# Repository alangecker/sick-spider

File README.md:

# SICK Spider
A new board design for the amazing [COATI Spider project](https://coati.pimienta.org/electronics/spider/), a small portable device for simultaneous interpretation.

## Changes compared to the COATI spider
- way less noise
- battery level indicator
- better gain control range
- USB-C port for power supply
- way longer battery runtime (8-50h)
- easier available components

## Costs
- roughly 20€ for a spider without accessories
- An existing COATI spider case can be reused, only one additional cutout for the USB-C port is required.

## Case
The files for 3D printing a case can be found here:
https://github.com/alangecker/spider-case

## Documents & How-To's

#### Version 1.2 (Documents work in progress)
- [Changelog](./CHANGELOG.md)
- Ordering
  * [Parts list](https://pad.kanthaus.online/sick-spider-parts-list?view)
  * Gerber files: [JLCPCB](https://alangecker.github.io/sick-spider/output/1.2/JLCPCB/spider2-JLCPCB.zip)
- Building instructions
    * [Part 1: soldering “SMD” components](https://pad.kanthaus.online/sick-spider-instructions-part1?view)
    * [Part 2: soldering "trough hole" components](https://pad.kanthaus.online/sick-spider-instructions-part2?view)
- [Debugging](https://pad.kanthaus.online/sick-spider-instructions-debugging?view)
- [Boardview and BOM](https://alangecker.github.io/sick-spider/output/1.2/spider2-ibom.html)
- [Schematic](https://alangecker.github.io/sick-spider/output/1.2/spider2-schematic.pdf)

#### Version 1.1
- [Changelog](./CHANGELOG.md)
- Ordering
  * [Parts list](./docs/v1.1/partslist.md)
  * Gerber files: [JLCPCB](https://alangecker.github.io/sick-spider/output/1.1c/JLCPCB/spider2-JLCPCB.zip)
- Building instructions
    * [Part 1: soldering “SMD” components](./docs/v1.1/part1-smd.md)
    * [Part 2: soldering "trough hole" components](./docs/v1.1/part2-throughhole.md)
- [Boardview and BOM](https://alangecker.github.io/sick-spider/output/1.1c/spider2-ibom.html)
- [Schematic](https://alangecker.github.io/sick-spider/output/1.1c/spider2-schematic.pdf)

#### Version 1.0
- Ordering
  * [Parts list](./docs/v1.0/partslist.md)
  * Gerber files: [JLCPCB](https://alangecker.github.io/sick-spider/output/1.0/JLCPCB/spider2-JLCPCB.zip)
- Building instructions
    * [Part 1: soldering “SMD” components](./docs/v1.0/part1-smd.md)
    * [Part 2: soldering "trough hole" components](./docs/v1.0/part2-throughhole.md)
    * [Part 3: building the case](https://pad.kanthaus.online/sick-spider-instructions-part3?view)
- [Debugging](./docs/v1.0/debugging.md)
- [Boardview and BOM](https://alangecker.github.io/sick-spider/output/1.0/spider2-ibom.html)
- [Schematic](https://alangecker.github.io/sick-spider/output/1.0/spider2-schematic.pdf)

## License
GPLv3 (=open source♥)

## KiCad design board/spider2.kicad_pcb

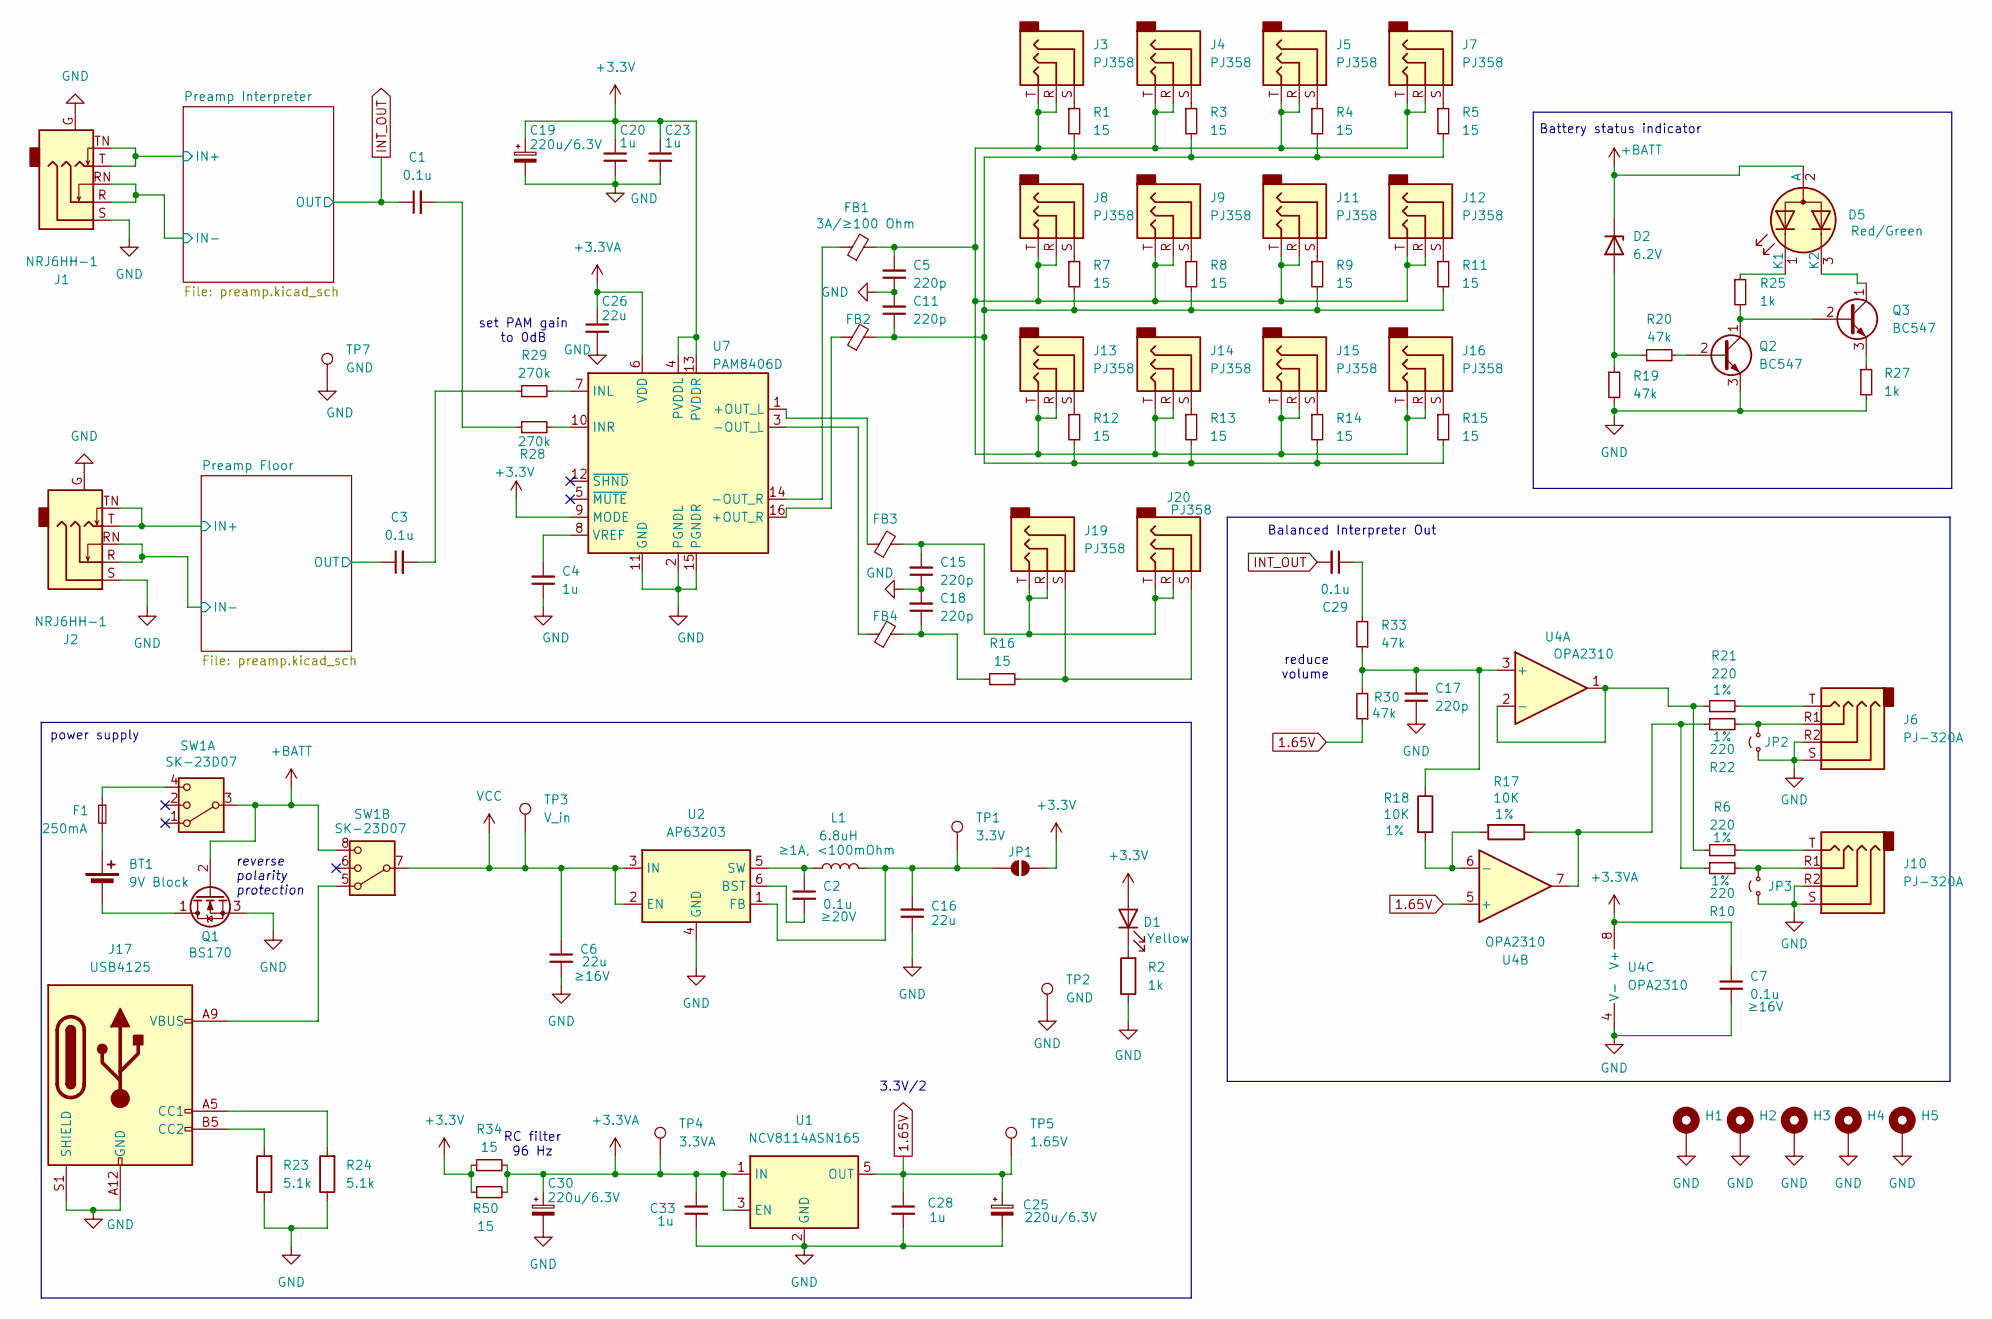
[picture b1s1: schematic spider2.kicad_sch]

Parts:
BT1: 9V Block; PinHeader_1x02_P2.54mm_Vertical
C1, C3, C7, C29: 0.1u; C_Disc_D3.0mm_W2.0mm_P2.50mm
C2: 0.1u; C_1206_3216Metric_Pad1.33x1.80mm_HandSolder
C4, C20, C23, C28, C33: 1u; C_Disc_D3.0mm_W2.0mm_P2.50mm
C5, C11, C15, C17, C18: 220p; C_Disc_D3.0mm_W2.0mm_P2.50mm
C6, C16, C26: 22u; C_1206_3216Metric_Pad1.33x1.80mm_HandSolder
C19, C25, C30: 220u/6.3V; CP_Radial_D6.3mm_P2.50mm
D1: Yellow; LED_D5.0mm_FlatTop
D2: 6.2V; D_DO-35_SOD27_P7.62mm_Horizontal
D5: Red/Green; LED_D5.0mm-3
F1: 250mA; Fuse_1206_3216Metric_Pad1.42x1.75mm_HandSolder
FB1, FB2, FB3, FB4: 3A/≥100 Ohm; L_Axial_L7.0mm_D3.3mm_P10.16mm_Horizontal_Fastron_MICC
H1, H2, H3, H4, H5: MountingHole_3.2mm_M3_Pad_Via
J1, J2: NRJ6HH-1; Jack_6.35mm_Neutrik_NRJ6HH-1_Horizontal
J3, J4, J5, J7, J8, J9, J11, J12, J13, J14, J15, J16, J19, J20: PJ358; Jack_3.5mm_Hybrid_PJ358_20-1655
J6, J10: PJ-320A; Jack_3.5mm_PJ320A
J17: USB4125; USB_C_Receptacle_GCT_USB4125-xx-x_6P_TopMnt_Horizontal
JP1, JP2, JP3: SolderJumper-2_P1.3mm_Open_RoundedPad1.0x1.5mm
L1: 6.8uH; L_Bourns_SRN6045TA
Q1: BS170; TO-92_Inline_Wide
Q2, Q3: BC547; TO-92_Inline_Wide
R1, R3, R4, R5, R7, R8, R9, R11, R12, R13, R14, R15, R16, R34, R50: 15; R_Axial_DIN0207_L6.3mm_D2.5mm_P10.16mm_Horizontal
R2, R25, R27: 1k; R_Axial_DIN0207_L6.3mm_D2.5mm_P10.16mm_Horizontal
R6, R10, R21, R22: 220; R_Axial_DIN0204_L3.6mm_D1.6mm_P5.08mm_Horizontal
R17, R18: 10K; R_Axial_DIN0204_L3.6mm_D1.6mm_P5.08mm_Horizontal
R19, R20, R30, R33: 47k; R_Axial_DIN0207_L6.3mm_D2.5mm_P10.16mm_Horizontal
R23, R24: 5.1k; R_Axial_DIN0207_L6.3mm_D2.5mm_P10.16mm_Horizontal
R28, R29: 270k; R_Axial_DIN0207_L6.3mm_D2.5mm_P7.62mm_Horizontal
SW1: SK-23D07
TP1: 3.3V; TestPoint_THTPad_1.5x1.5mm_Drill0.7mm
TP2: GND; TestPoint_THTPad_2.5x2.5mm_Drill1.2mm
TP3: V_in; TestPoint_THTPad_1.5x1.5mm_Drill0.7mm
TP4: 3.3VA; TestPoint_THTPad_1.5x1.5mm_Drill0.7mm
TP5: 1.65V; TestPoint_THTPad_1.5x1.5mm_Drill0.7mm
TP7: GND; TestPoint_THTPad_4.0x4.0mm_Drill2.0mm
U1: NCV8114ASN165; TSOT-23-5
U2: AP63203; TSOT-23-6
U4: OPA2310; SOIC-8_3.9x4.9mm_P1.27mm
U7: PAM8406D; SOP-16_3.9x9.9mm_P1.27mm

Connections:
1.65V: C25.1, C28.1, R30.1, TP5.1, U1.5 (OUT), U4.5 (+); also elsewhere on the board
+3.3V: C19.1, C20.1, C23.1, D1.2 (A), JP1.2 (B), R34.1, R50.1, U7.4 (PVDDL), U7.9 (MODE), U7.13 (PVDDR)
+3.3VA: C7.1, C26.1, C30.1, C33.1, R34.2, R50.2, TP4.1, U1.1 (IN), U1.3 (EN), U4.8 (V+), U7.6 (VDD); also elsewhere on the board
+BATT: D2.1 (K), D5.2 (A), Q1.2 (G), SW1.3, SW1.8
/Preamp Floor/IN+: J2.T, J2.TN; also elsewhere on the board
/Preamp Floor/IN-: J2.R, J2.RN; also elsewhere on the board
/Preamp Floor/OUT: C3.1; also elsewhere on the board
/Preamp Interpreter/IN+: J1.T, J1.TN; also elsewhere on the board
/Preamp Interpreter/IN-: J1.R, J1.RN; also elsewhere on the board
GND: C4.1, C5.1, C6.2, C7.2, C11.2, C15.1, C16.1, C17.1, C18.2, C19.2, C20.2, C23.2, C25.2, C26.2, C28.2, C30.2, C33.2, H1.1, H2.1, H3.1, H4.1, H5.1, J1.G, J1.S, J2.G, J2.S, J6.R2, J6.S, J10.R2, J10.S, J17.A12 (GND), J17.B12 (GND), J17.S1 (SHIELD), JP2.1 (A), JP3.1 (A), Q1.3 (S), Q2.3 (E), R2.1, R19.2, R23.1, R24.1, R27.2, TP2.1, TP7.1, U1.2 (GND), U2.4 (GND), U4.4 (V-), U7.2 (PGNDL), U7.11 (GND), U7.15 (PGNDR); also elsewhere on the board
INT_OUT: C1.1, C29.2; also elsewhere on the board
unnamed: BT1.1 (+), F1.2
unnamed: BT1.2 (-), Q1.1 (D)
unnamed: C1.2, R28.1
unnamed: C3.2, R29.1
unnamed: C5.2, FB1.2, J3.R, J3.T, J4.R, J4.T, J5.R, J5.T, J7.R, J7.T, J8.R, J8.T, J9.R, J9.T, J11.R, J11.T, J12.R, J12.T, J13.R, J13.T, J14.R, J14.T, J15.R, J15.T, J16.R, J16.T
unnamed: C11.1, FB2.2, R1.2, R3.2, R4.2, R5.2, R7.2, R8.2, R9.2, R11.2, R12.2, R13.2, R14.2, R15.2
unnamed: C15.2, FB3.2, J19.R, J19.T, J20.R, J20.T
unnamed: C18.1, FB4.2, R16.1
unnamed: C29.1, R33.2
unnamed: D1.1 (K), R2.2
unnamed: D2.2 (A), R19.1, R20.1
unnamed: D5.1 (K1), R25.1
unnamed: D5.3 (K2), Q3.1 (C)
unnamed: F1.1, SW1.4
unnamed: J3.S, R1.1
unnamed: J4.S, R3.1
unnamed: J5.S, R4.1
unnamed: J6.T, R21.2
unnamed: J7.S, R5.1
unnamed: J8.S, R7.1
unnamed: J9.S, R8.1
unnamed: J10.T, R6.2
unnamed: J11.S, R9.1
unnamed: J12.S, R11.1
unnamed: J13.S, R12.1
unnamed: J14.S, R13.1
unnamed: J15.S, R14.1
unnamed: J16.S, R15.1
unnamed: J17.A5 (CC1), R24.2
unnamed: J17.B5 (CC2), R23.2
unnamed: J17.A9 (VBUS), J17.B9 (VBUS), SW1.5
unnamed: J19.S, J20.S, R16.2
unnamed: C16.2, JP1.1 (A), L1.2, TP1.1, U2.1 (FB)
unnamed: J6.R1, JP2.2 (B), R22.2
unnamed: J10.R1, JP3.2 (B), R10.2
unnamed: Q2.2 (B), R20.2
unnamed: Q2.1 (C), Q3.2 (B), R25.2
unnamed: Q3.3 (E), R27.1
unnamed: R10.1, R17.1, R22.1, U4.7
unnamed: C2.2, U2.6 (BST)
unnamed: C2.1, L1.1, U2.5 (SW)
unnamed: C17.2, R18.1, R30.2, R33.1, U4.3 (+)
unnamed: R6.1, R21.1, U4.1, U4.2 (-)
unnamed: R17.2, R18.2, U4.6 (-)
unnamed: FB3.1, U7.1 (+OUT_L)
unnamed: FB2.1, U7.16 (+OUT_R)
unnamed: FB4.1, U7.3 (-OUT_L)
unnamed: FB1.1, U7.14 (-OUT_R)
unnamed: R29.2, U7.7 (INL)
unnamed: R28.2, U7.10 (INR)
unnamed: C4.2, U7.8 (VREF)
VCC: C6.1, SW1.7, TP3.1, U2.2 (EN), U2.3 (IN)

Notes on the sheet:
reduce volume
Balanced Interpreter Out
set PAM gain to 0dB
reverse polarity protection
Battery status indicator
3.3V/2
RC filter 96 Hz
power supply

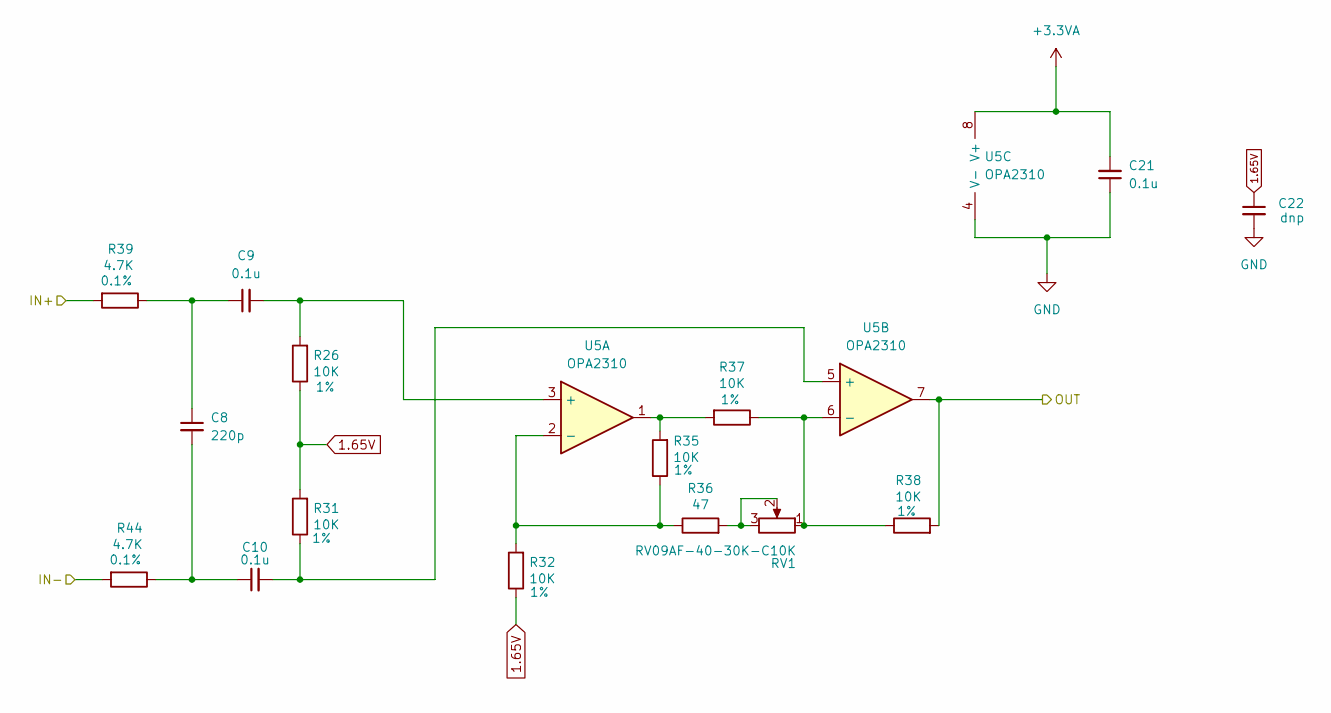
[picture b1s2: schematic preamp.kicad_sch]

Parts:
C8: 220p; C_Disc_D3.0mm_W2.0mm_P2.50mm
C9, C10, C21: 0.1u; C_Disc_D3.0mm_W2.0mm_P2.50mm
C22: dnp; C_Disc_D3.0mm_W2.0mm_P2.50mm
R26, R31, R32, R35, R37, R38: 10K; R_Axial_DIN0204_L3.6mm_D1.6mm_P5.08mm_Horizontal
R36: 47; R_Axial_DIN0204_L3.6mm_D1.6mm_P5.08mm_Horizontal
R39, R44: 4.7K; R_Axial_DIN0207_L6.3mm_D2.5mm_P7.62mm_Horizontal
RV1: RV09AF-40-30K-C10K; Potentiometer_Bourns_PTV09A-1_Single_Vertical
U5: OPA2310; SOIC-8_3.9x4.9mm_P1.27mm

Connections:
1.65V: C22.1, R26.1, R31.2, R32.1; also elsewhere on the board
+3.3VA: C21.2, U5.8 (V+); also elsewhere on the board
/Preamp Interpreter/IN+: R39.2; also elsewhere on the board
/Preamp Interpreter/IN-: R44.2; also elsewhere on the board
GND: C21.1, C22.2, U5.4 (V-); also elsewhere on the board
INT_OUT: R38.2, U5.7; also elsewhere on the board
unnamed: C8.1, C9.1, R39.1
unnamed: C8.2, C10.1, R44.1
unnamed: R35.2, R37.2, U5.1
unnamed: R36.2, RV1.2, RV1.3
unnamed: C9.2, R26.2, U5.3 (+)
unnamed: R32.2, R35.1, R36.1, U5.2 (-)
unnamed: C10.2, R31.1, U5.5 (+)
unnamed: R37.1, R38.1, RV1.1, U5.6 (-)

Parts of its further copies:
C12: 220p; C_Disc_D3.0mm_W2.0mm_P2.50mm
C13, C14, C27: 0.1u; C_Disc_D3.0mm_W2.0mm_P2.50mm
C24: dnp; C_Disc_D3.0mm_W2.0mm_P2.50mm
R40, R41, R42, R45, R47, R48: 10K; R_Axial_DIN0204_L3.6mm_D1.6mm_P5.08mm_Horizontal
R43, R49: 4.7K; R_Axial_DIN0207_L6.3mm_D2.5mm_P7.62mm_Horizontal
R46: 47; R_Axial_DIN0204_L3.6mm_D1.6mm_P5.08mm_Horizontal
RV2: RV09AF-40-30K-C10K; Potentiometer_Bourns_PTV09A-1_Single_Vertical
U6: OPA2310; SOIC-8_3.9x4.9mm_P1.27mm

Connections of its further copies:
1.65V: C24.1, R40.1, R41.2, R42.1; also elsewhere on the board
+3.3VA: C27.2, U6.8 (V+); also elsewhere on the board
/Preamp Floor/IN+: R43.2; also elsewhere on the board
/Preamp Floor/IN-: R49.2; also elsewhere on the board
/Preamp Floor/OUT: R48.2, U6.7; also elsewhere on the board
GND: C24.2, C27.1, U6.4 (V-); also elsewhere on the board
unnamed: C12.1, C13.1, R43.1
unnamed: C12.2, C14.1, R49.1
unnamed: R45.2, R47.2, U6.1
unnamed: R46.2, RV2.2, RV2.3
unnamed: C13.2, R40.2, U6.3 (+)
unnamed: R42.2, R45.1, R46.1, U6.2 (-)
unnamed: C14.2, R41.1, U6.5 (+)
unnamed: R47.1, R48.1, RV2.1, U6.6 (-)

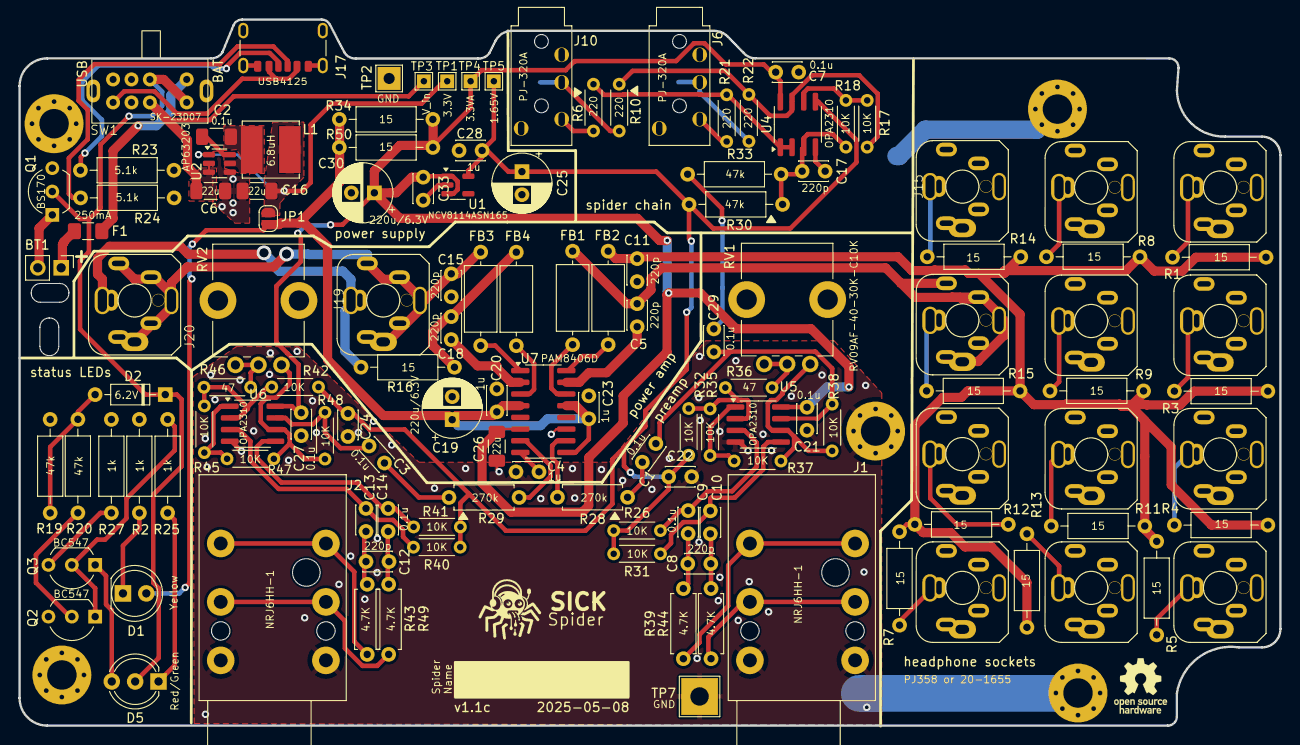
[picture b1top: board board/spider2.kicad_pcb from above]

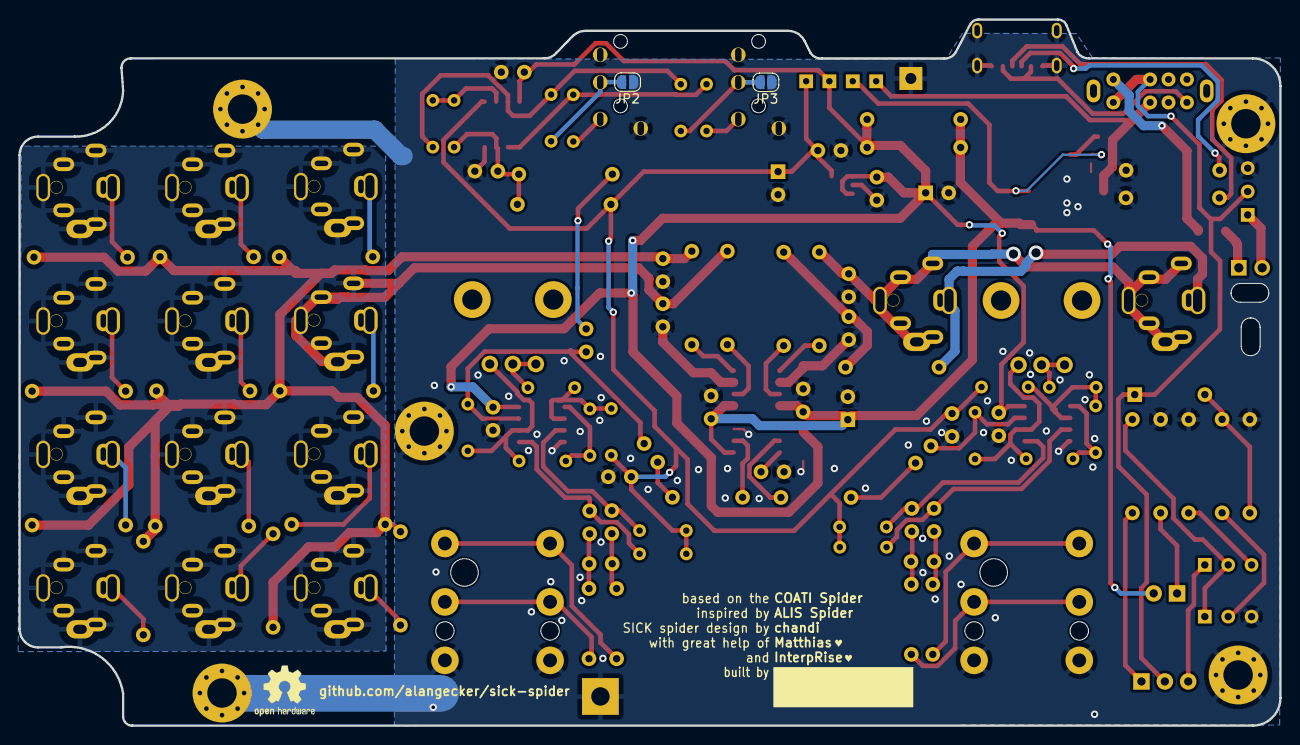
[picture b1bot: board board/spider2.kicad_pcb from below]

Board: 2 copper layers, 137.0 x 76.7 mm, 138 parts (3 on the bottom side), 79 nets.

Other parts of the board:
LOGO1: OSHW-Logo_5.7x6mm_SilkScreen
LOGO2: OSHW-Logo2_7.3x6mm_SilkScreen

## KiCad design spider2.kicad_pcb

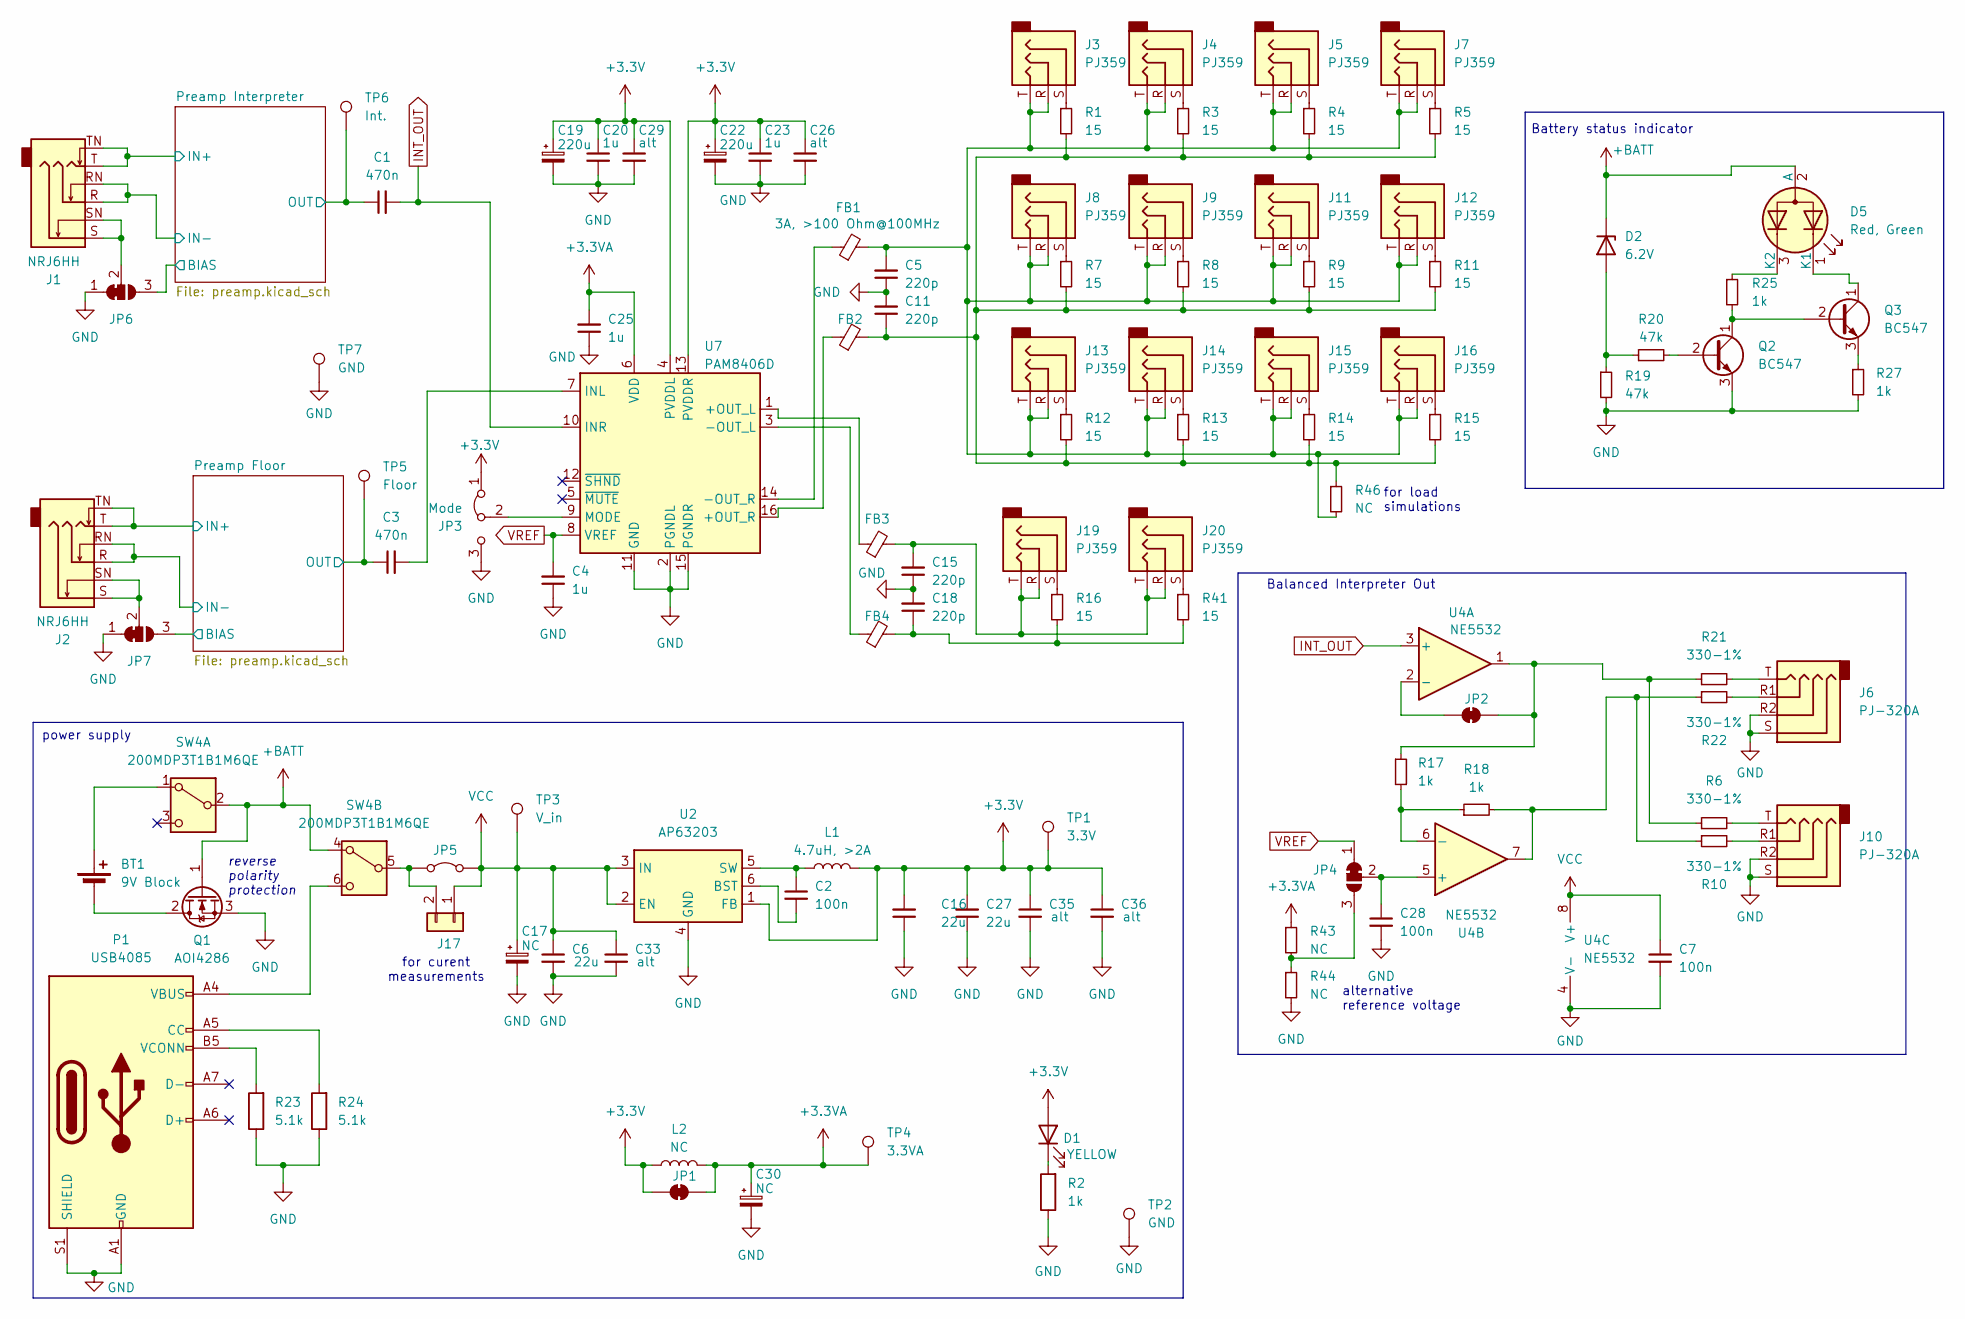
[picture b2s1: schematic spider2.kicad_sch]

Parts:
BT1: 9V Block; PinHeader_1x02_P2.54mm_Vertical
C1, C3: 470n; C_Disc_D5.1mm_W3.2mm_P5.00mm
C2, C7, C28: 100n; C_Disc_D5.1mm_W3.2mm_P5.00mm
C4, C20, C23, C25: 1u; C_Disc_D5.1mm_W3.2mm_P5.00mm
C5, C11, C15, C18: 220p; C_Disc_D5.1mm_W3.2mm_P5.00mm
C6, C16, C27: 22u; C_Disc_D5.1mm_W3.2mm_P5.00mm
C17, C30: NC; CP_Radial_D6.3mm_P2.50mm
C19, C22: 220u; CP_Radial_D6.3mm_P2.50mm
C26, C29: alt; C_0805_2012Metric_Pad1.18x1.45mm_HandSolder
C33, C35, C36: alt; C_1210_3225Metric_Pad1.33x2.70mm_HandSolder
D1: YELLOW; LED_D5.0mm_FlatTop
D2: 6.2V; D_DO-35_SOD27_P7.62mm_Horizontal
D5: Red, Green; LED_D5.0mm-3
FB1, FB2, FB3, FB4: 3A, >100 Ohm@100MHz; L_Axial_L7.0mm_D3.3mm_P10.16mm_Horizontal_Fastron_MICC
J1, J2: NRJ6HH; Jack_6.35mm_Neutrik_NRJ6HH_Horizontal
J3, J4, J5, J7, J8, J9, J11, J12, J13, J14, J15, J16, J19, J20: PJ359; Jack_3.5mm_PJ359
J6, J10: PJ-320A; Jack_3.5mm_PJ320A
J17: A; PinHeader_1x02_P2.54mm_Vertical
JP1, JP2: SolderJumper_2_Bridged; SolderJumper-2_P1.3mm_Bridged_RoundedPad1.0x1.5mm
JP3: Mode; SolderJumper-3_P1.3mm_Bridged12_RoundedPad1.0x1.5mm
JP4, JP6, JP7: SolderJumper_3_Bridged12; SolderJumper-3_P1.3mm_Bridged12_RoundedPad1.0x1.5mm
JP5: Jumper_2_Bridged; SolderJumper-2_P1.3mm_Bridged_RoundedPad1.0x1.5mm
L1: 4.7uH, >2A; L_Radial_D8.7mm_P5.00mm_Fastron_07HCP
L2: NC; L_Axial_L5.3mm_D2.2mm_P10.16mm_Horizontal_Vishay_IM-1
P1: USB4085; USB_C_Receptacle_GCT_USB4085
Q1: AOI4286; TO-251-3_Vertical
Q2, Q3: BC547; TO-92_Inline
R1, R3, R4, R5, R7, R8, R9, R11, R12, R13, R14, R15, R16, R41: 15; R_Axial_DIN0207_L6.3mm_D2.5mm_P10.16mm_Horizontal
R2, R17, R18, R25, R27: 1k; R_Axial_DIN0207_L6.3mm_D2.5mm_P10.16mm_Horizontal
R6, R10, R21, R22: 330-1%; R_Axial_DIN0207_L6.3mm_D2.5mm_P10.16mm_Horizontal
R19, R20: 47k; R_Axial_DIN0207_L6.3mm_D2.5mm_P10.16mm_Horizontal
R23, R24: 5.1k; R_Axial_DIN0207_L6.3mm_D2.5mm_P10.16mm_Horizontal
R43, R44: NC; R_Axial_DIN0207_L6.3mm_D2.5mm_P10.16mm_Horizontal
R46: NC; R_Axial_Power_L25.0mm_W9.0mm_P7.62mm_Vertical
SW4: 200MDP3T1B1M6QE; SW_Push_2P2T_Vertical_E-Switch_800UDP8P1A1M6
TP1: 3.3V; TestPoint_THTPad_1.5x1.5mm_Drill0.7mm
TP2: GND; TestPoint_THTPad_2.5x2.5mm_Drill1.2mm
TP3: V_in; TestPoint_THTPad_1.5x1.5mm_Drill0.7mm
TP4: 3.3VA; TestPoint_THTPad_1.5x1.5mm_Drill0.7mm
TP5: Floor; TestPoint_THTPad_1.5x1.5mm_Drill0.7mm
TP6: Int.; TestPoint_THTPad_1.5x1.5mm_Drill0.7mm
TP7: GND; TestPoint_THTPad_4.0x4.0mm_Drill2.0mm
U2: AP63203; TSOT-23-6
U4: NE5532; DIP-8_W7.62mm
U7: PAM8406D; SOP-16_3.9x9.9mm_P1.27mm

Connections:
+3.3V: C16.2, C19.1, C20.1, C22.1, C23.1, C26.1, C27.2, C29.1, C35.1, C36.1, D1.2 (A), JP1.1 (A), JP3.1 (A), L1.2, L2.1, TP1.1, U2.1 (FB), U7.4 (PVDDL), U7.13 (PVDDR)
+BATT: D2.1 (K), D5.2 (A), Q1.1 (G), SW4.2 (B), SW4.4 (A)
/Preamp Floor/BIAS: JP7.3 (B); also elsewhere on the board
/Preamp Floor/IN+: J2.T, J2.TN; also elsewhere on the board
/Preamp Floor/IN-: J2.R, J2.RN; also elsewhere on the board
/Preamp Floor/OUT: C3.1, TP5.1; also elsewhere on the board
/Preamp Interpreter/BIAS: JP6.3 (B); also elsewhere on the board
/Preamp Interpreter/IN+: J1.T, J1.TN; also elsewhere on the board
/Preamp Interpreter/IN-: J1.R, J1.RN; also elsewhere on the board
/Preamp Interpreter/OUT: C1.1, TP6.1; also elsewhere on the board
GND: C4.1, C5.1, C6.2, C7.2, C11.2, C15.1, C16.1, C17.2, C18.2, C19.2, C20.2, C22.2, C23.2, C25.1, C26.2, C27.1, C28.2, C29.2, C30.2, C33.2, C35.2, C36.2, J6.R2, J6.S, J10.R2, J10.S, JP3.3 (B), JP6.1 (A), JP7.1 (A), P1.A1 (GND), P1.A12 (GND), P1.B1 (GND), P1.B12 (GND), P1.S1 (SHIELD), Q1.3 (S), Q2.3 (E), R2.1, R19.2, R23.1, R24.1, R27.2, R44.2, TP2.1, TP7.1, U2.4 (GND), U4.4 (V-), U7.2 (PGNDL), U7.11 (GND), U7.15 (PGNDR); also elsewhere on the board
INT_OUT: C1.2, U4.3 (+), U7.10 (INR)
unnamed: BT1.1 (+), SW4.1 (A)
unnamed: BT1.2 (-), Q1.2 (D)
unnamed: C5.2, FB1.2, J3.R, J3.T, J4.R, J4.T, J5.R, J5.T, J7.R, J7.T, J8.R, J8.T, J9.R, J9.T, J11.R, J11.T, J12.R, J12.T, J13.R, J13.T, J14.R, J14.T, J15.R, J15.T, J16.R, J16.T, R46.2
unnamed: C11.1, FB2.2, R1.2, R3.2, R4.2, R5.2, R7.2, R8.2, R9.2, R11.2, R12.2, R13.2, R14.2, R15.2, R46.1
unnamed: C15.2, FB3.2, J19.R, J19.T, J20.R, J20.T
unnamed: C18.1, FB4.2, R16.2, R41.2
unnamed: D1.1 (K), R2.2
unnamed: D2.2 (A), R19.1, R20.1
unnamed: D5.1 (K1), Q3.1 (C)
unnamed: D5.3 (K2), R25.1
unnamed: J3.S, R1.1
unnamed: J4.S, R3.1
unnamed: J5.S, R4.1
unnamed: J6.R1, R22.2
unnamed: J6.T, R21.2
unnamed: J7.S, R5.1
unnamed: J8.S, R7.1
unnamed: J9.S, R8.1
unnamed: J10.R1, R10.2
unnamed: J10.T, R6.2
unnamed: J11.S, R9.1
unnamed: J12.S, R11.1
unnamed: J13.S, R12.1
unnamed: J14.S, R13.1
unnamed: J15.S, R14.1
unnamed: J16.S, R15.1
unnamed: J17.2, JP5.1 (A), SW4.5 (B)
unnamed: J19.S, R16.1
unnamed: J20.S, R41.1
unnamed: JP2.1 (A), U4.2 (-)
unnamed: JP2.2 (B), R6.1, R17.1, R21.1, U4.1
unnamed: JP3.2 (C), U7.9 (MODE)
unnamed: JP4.3 (B), R43.2, R44.1
unnamed: C28.1, JP4.2 (C), U4.5 (+)
unnamed: J1.S, J1.SN, JP6.2 (C)
unnamed: J2.S, J2.SN, JP7.2 (C)
unnamed: P1.A5 (CC), R24.2
unnamed: P1.B5 (VCONN), R23.2
unnamed: Q2.2 (B), R20.2
unnamed: Q2.1 (C), Q3.2 (B), R25.2
unnamed: Q3.3 (E), R27.1
unnamed: R10.1, R18.2, R22.1, U4.7
unnamed: P1.A4 (VBUS), P1.A9 (VBUS), P1.B4 (VBUS), P1.B9 (VBUS), SW4.6 (C)
unnamed: C2.2, U2.6 (BST)
unnamed: C2.1, L1.1, U2.5 (SW)
unnamed: R17.2, R18.1, U4.6 (-)
unnamed: FB3.1, U7.1 (+OUT_L)
unnamed: FB2.1, U7.16 (+OUT_R)
unnamed: FB4.1, U7.3 (-OUT_L)
unnamed: FB1.1, U7.14 (-OUT_R)
unnamed: C3.2, U7.7 (INL)
VCC: C6.1, C7.1, C17.1, C33.1, J17.1, JP5.2 (B), TP3.1, U2.2 (EN), U2.3 (IN), U4.8 (V+)
VREF: C4.2, JP4.1 (A), U7.8 (VREF)

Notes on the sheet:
Balanced Interpreter Out
alternative reference voltage
reverse polarity protection
for load simulations
Battery status indicator
for curent measurements
power supply

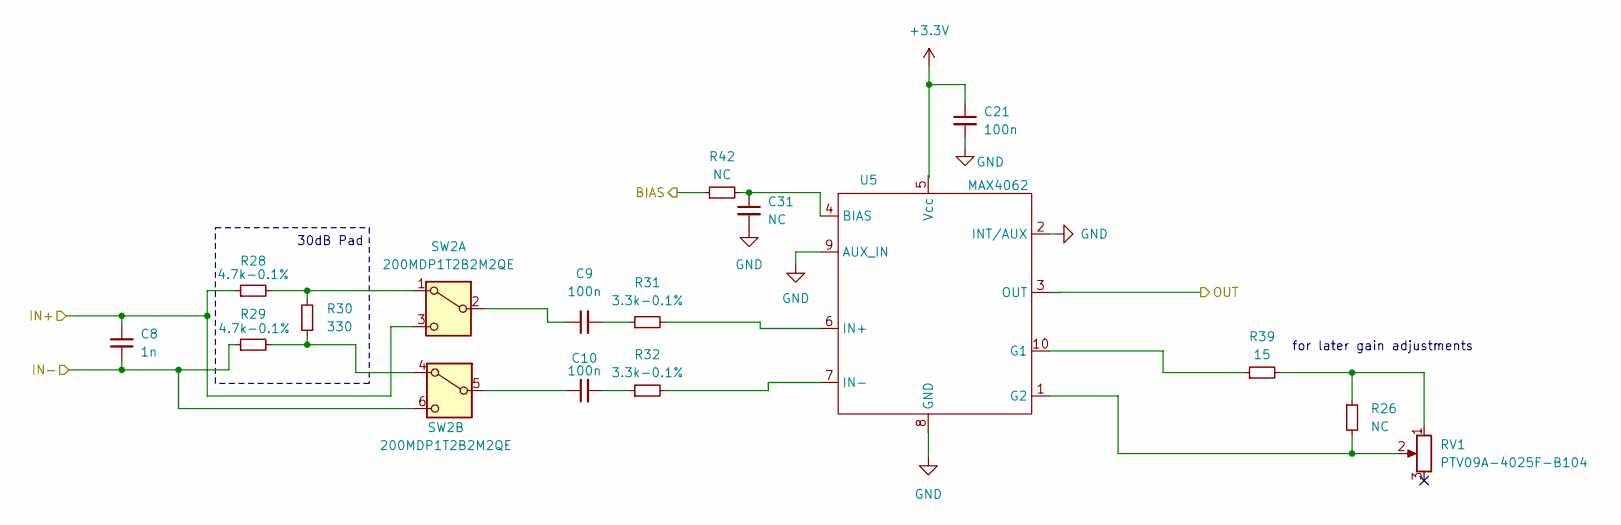
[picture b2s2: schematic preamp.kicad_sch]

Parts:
C8: 1n; C_Disc_D5.1mm_W3.2mm_P5.00mm
C9, C10, C21: 100n; C_Disc_D5.1mm_W3.2mm_P5.00mm
C31: NC; C_0805_2012Metric_Pad1.18x1.45mm_HandSolder
R26: NC; R_Axial_DIN0207_L6.3mm_D2.5mm_P10.16mm_Horizontal
R28, R29: 4.7k-0.1%; R_Axial_DIN0207_L6.3mm_D2.5mm_P10.16mm_Horizontal
R30: 330; R_Axial_DIN0207_L6.3mm_D2.5mm_P10.16mm_Horizontal
R31, R32: 3.3k-0.1%; R_Axial_DIN0207_L6.3mm_D2.5mm_P10.16mm_Horizontal
R39: 15; R_Axial_DIN0207_L6.3mm_D2.5mm_P10.16mm_Horizontal
R42: NC; R_0805_2012Metric_Pad1.20x1.40mm_HandSolder
RV1: PTV09A-4025F-B104; Potentiometer_Bourns_PTV09A-1_Single_Vertical
SW2: 200MDP1T2B2M2QE; SW_PUSH_E-Switch_200MDPxTxBxM2
U5: MAX4062; MSOP-10_3x3mm_P0.5mm

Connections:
/Preamp Interpreter/BIAS: R42.1; also elsewhere on the board
/Preamp Interpreter/IN+: C8.1, R28.1, SW2.3 (C); also elsewhere on the board
/Preamp Interpreter/IN-: C8.2, R29.1, SW2.6 (C); also elsewhere on the board
/Preamp Interpreter/OUT: U5.3 (OUT); also elsewhere on the board
GND: C21.2, C31.2, U5.2 (INT/AUX), U5.8 (GND), U5.9 (AUX_IN); also elsewhere on the board
unnamed: C9.2, R31.1
unnamed: C10.2, R32.1
unnamed: R26.1, R39.2, RV1.1
unnamed: R28.2, R30.2, SW2.1 (A)
unnamed: C9.1, SW2.2 (B)
unnamed: R29.2, R30.1, SW2.4 (A)
unnamed: C10.1, SW2.5 (B)
unnamed: C31.1, R42.2, U5.4 (BIAS)
unnamed: R39.1, U5.10 (G1)
unnamed: R26.2, RV1.2, U5.1 (G2)
unnamed: R31.2, U5.6 (IN+)
unnamed: R32.2, U5.7 (IN-)

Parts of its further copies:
C12: 1n; C_Disc_D5.1mm_W3.2mm_P5.00mm
C13, C14, C24: 100n; C_Disc_D5.1mm_W3.2mm_P5.00mm
C32: NC; C_0805_2012Metric_Pad1.18x1.45mm_HandSolder
R33, R34: 4.7k-0.1%; R_Axial_DIN0207_L6.3mm_D2.5mm_P10.16mm_Horizontal
R38: NC; R_Axial_DIN0207_L6.3mm_D2.5mm_P10.16mm_Horizontal
R40: 15; R_Axial_DIN0207_L6.3mm_D2.5mm_P10.16mm_Horizontal
R45: NC; R_0805_2012Metric_Pad1.20x1.40mm_HandSolder
RV2: PTV09A-4025F-B104; Potentiometer_Bourns_PTV09A-1_Single_Vertical
U6: MAX4062; MSOP-10_3x3mm_P0.5mm

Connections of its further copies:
/Preamp Floor/BIAS: R45.1; also elsewhere on the board
/Preamp Floor/IN+: C12.1, R33.1; also elsewhere on the board
/Preamp Floor/IN-: C12.2, R34.1; also elsewhere on the board
/Preamp Floor/OUT: U6.3 (OUT); also elsewhere on the board
GND: C24.2, C32.2, U6.2 (INT/AUX), U6.8 (GND), U6.9 (AUX_IN); also elsewhere on the board
unnamed 18: C13.2; also elsewhere on the board
unnamed 19: C14.2; also elsewhere on the board
unnamed: R38.1, R40.2, RV2.1
unnamed 64: R33.2; also elsewhere on the board
unnamed 65: C13.1; also elsewhere on the board
unnamed 66: R34.2; also elsewhere on the board
unnamed 67: C14.1; also elsewhere on the board
unnamed: C32.1, R45.2, U6.4 (BIAS)
unnamed: R40.1, U6.10 (G1)
unnamed: R38.2, RV2.2, U6.1 (G2)
unnamed 80: U6.6 (IN+); also elsewhere on the board
unnamed 81: U6.7 (IN-); also elsewhere on the board

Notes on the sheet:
30dB Pad
for later gain adjustments

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
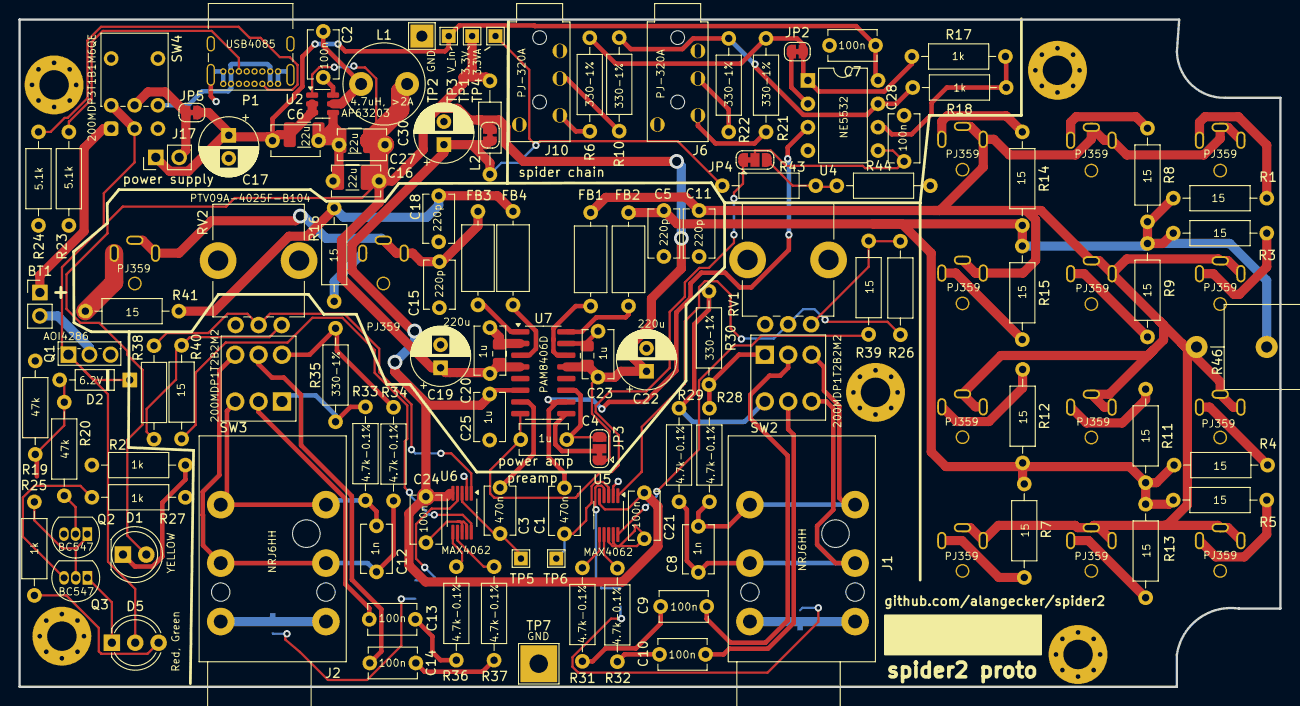
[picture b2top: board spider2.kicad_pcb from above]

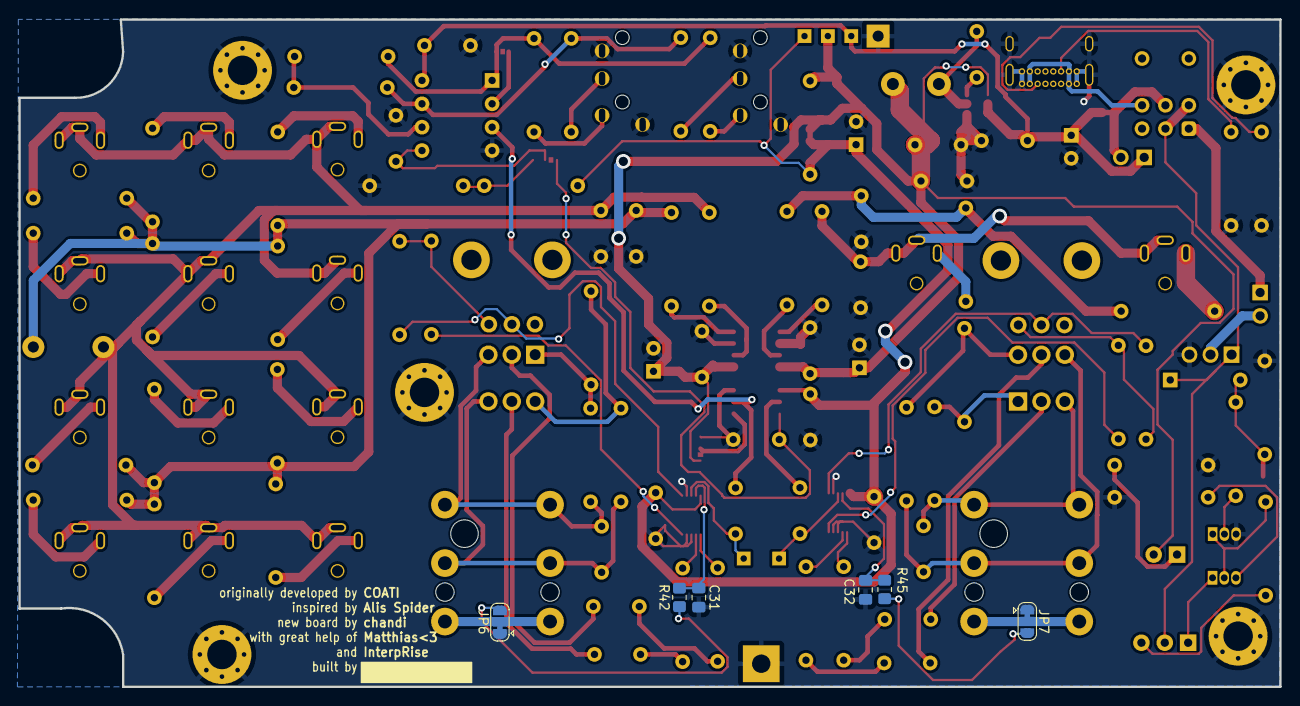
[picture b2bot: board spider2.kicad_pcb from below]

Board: 2 copper layers, 137.0 x 72.5 mm, 138 parts (6 on the bottom side), 90 nets.

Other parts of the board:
R35: 330-1%; R_Axial_DIN0207_L6.3mm_D2.5mm_P10.16mm_Horizontal
R36, R37: 4.7k-0.1%; R_Axial_DIN0207_L6.3mm_D2.5mm_P10.16mm_Horizontal
SW3: 200MDP1T2B2M2; SW_PUSH_E-Switch_200MDPxTxBxM2

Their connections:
/Preamp Floor/IN+: SW3.3 (C); also elsewhere on the board
/Preamp Floor/IN-: SW3.6 (C); also elsewhere on the board
unnamed 18: R36.1; also elsewhere on the board
unnamed 19: R37.1; also elsewhere on the board
unnamed 64: R35.2, SW3.1 (A); also elsewhere on the board
unnamed 65: SW3.2 (B); also elsewhere on the board
unnamed 66: R35.1, SW3.4 (A); also elsewhere on the board
unnamed 67: SW3.5 (B); also elsewhere on the board
unnamed 80: R36.2; also elsewhere on the board
unnamed 81: R37.2; also elsewhere on the board
